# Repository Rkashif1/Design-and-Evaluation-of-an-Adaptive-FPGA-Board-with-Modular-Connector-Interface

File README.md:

**Design and Evaluation of an Adaptive FPGA Board with Modular Connector Interface**

This repository contains the complete project files for the development of an adaptive FPGA board designed to interface with various sensor and actuator peripherals through dual high-density connectors. The FPGA module is implemented using the Xilinx Spartan-7 XC7S25 and follows a modular architecture that allows it to be plugged into different motherboards for dynamic reconfiguration.

📁 Contents include:

KiCad schematic and PCB layout files

LaTeX report and documentation

Schematics and 3D board Refrence Images

🛠️ Key tools used: KiCad, Xilinx Vivado, Git, LaTeX

📌 Developed as part of an academic project demonstrating real-world modular hardware design and reconfigurable embedded systems.

*3D rendered view of the adaptive FPGA board featuring dual high-density connectors and a Spartan-7 FPGA*

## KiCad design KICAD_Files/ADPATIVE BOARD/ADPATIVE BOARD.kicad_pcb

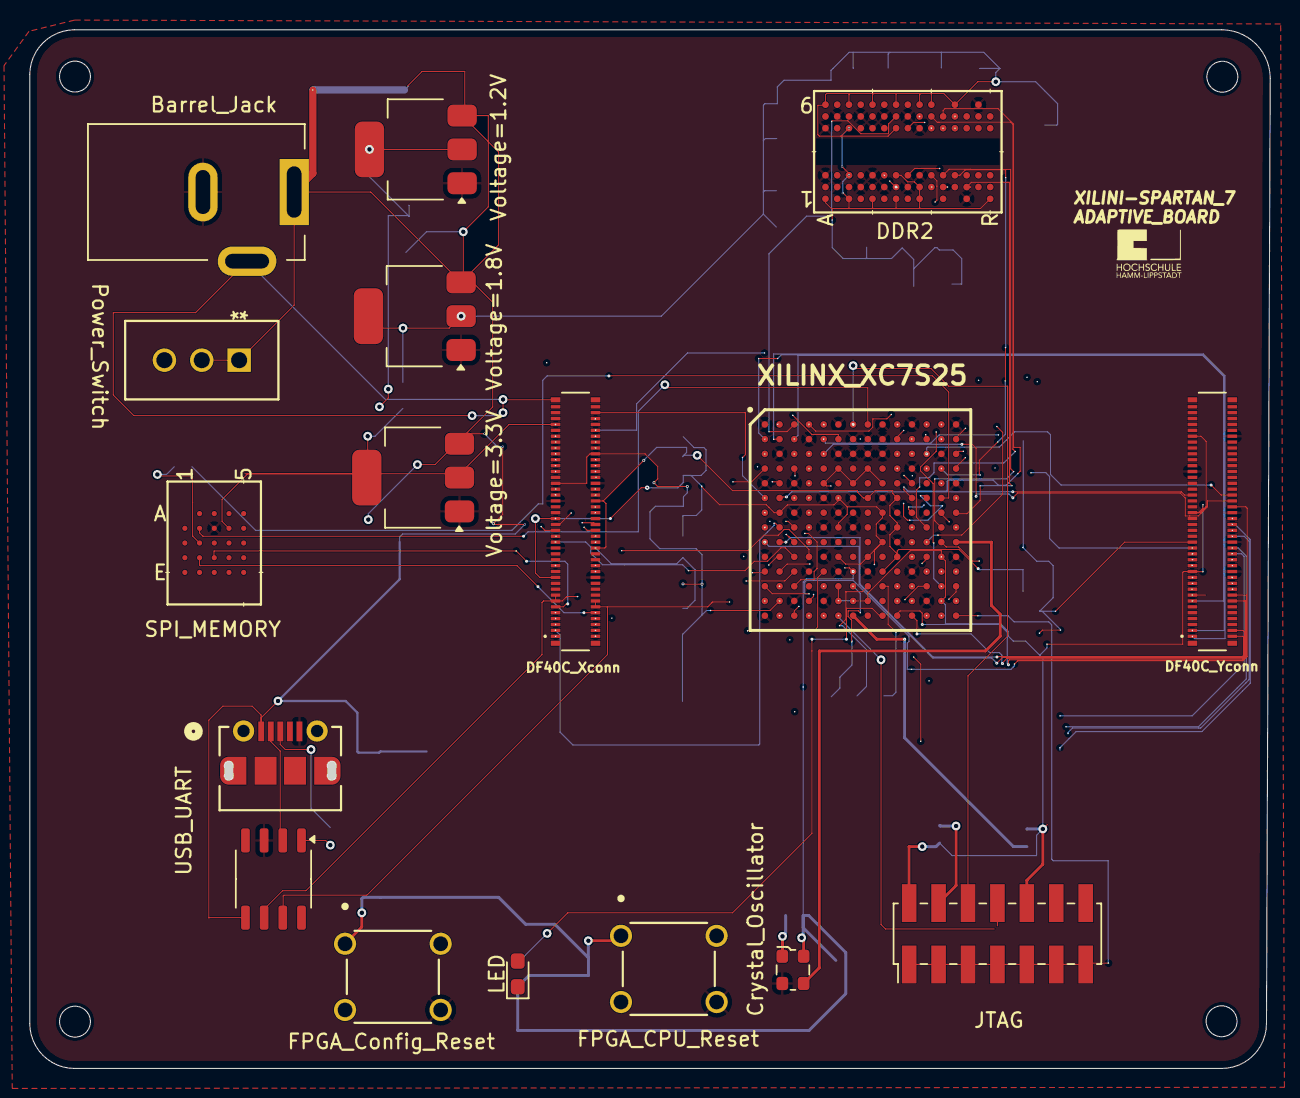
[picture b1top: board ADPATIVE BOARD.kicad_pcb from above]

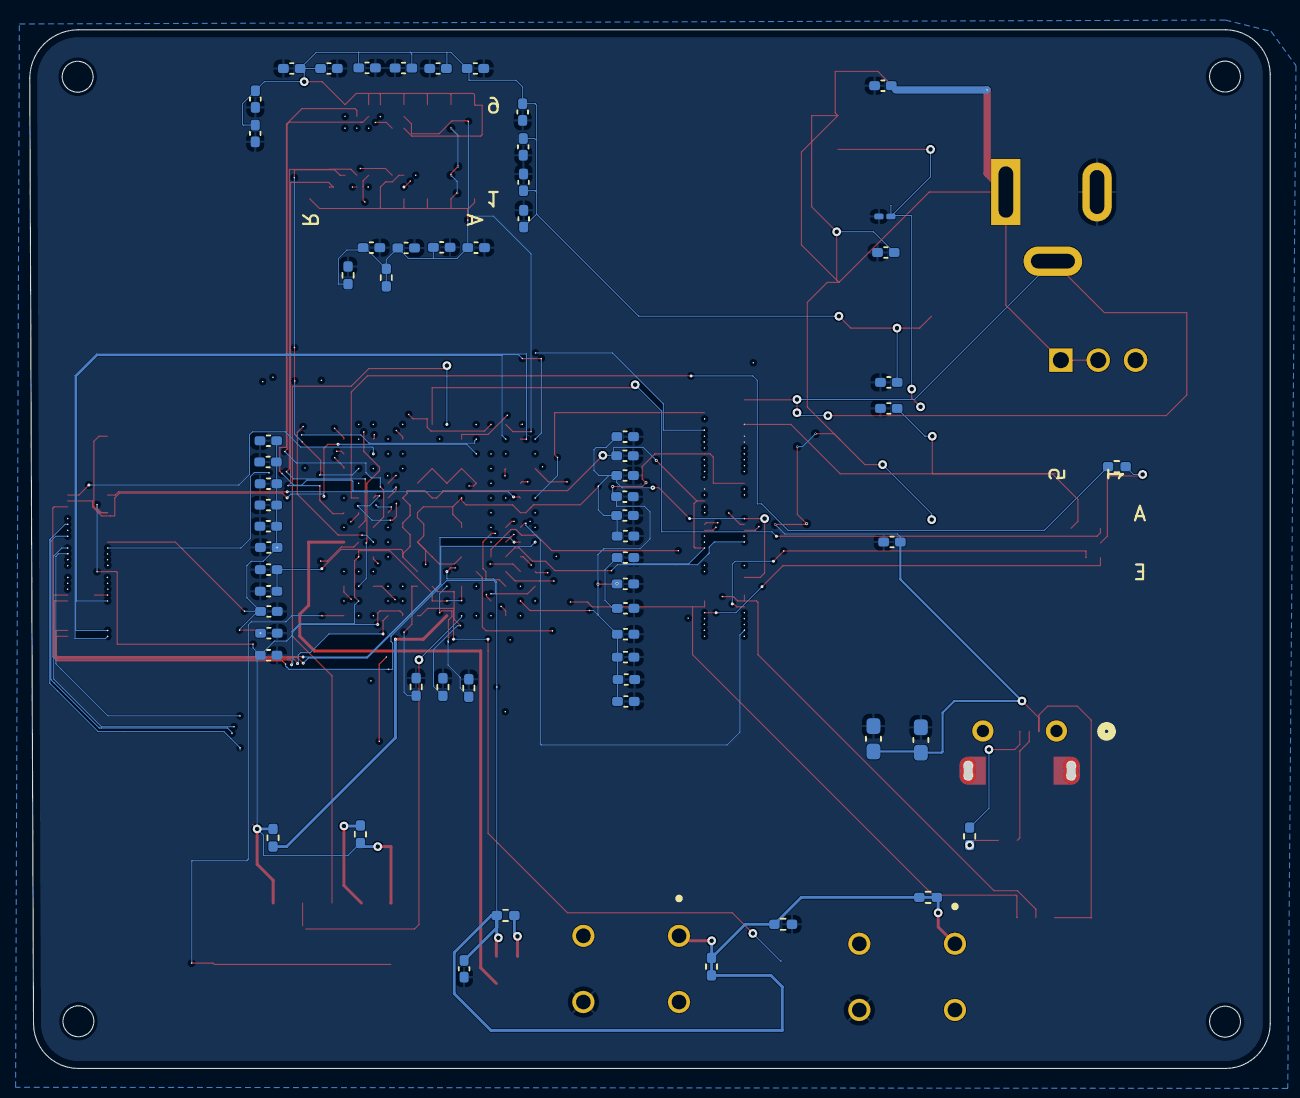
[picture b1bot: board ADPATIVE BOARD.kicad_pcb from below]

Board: 10 copper layers, 84.3 x 70.6 mm, 79 parts (62 on the bottom side), 118 nets.

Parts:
Barrel_Jack: BarrelJack_Kycon_KLDX-0202-xC_Horizontal
C1, C2, C3, C4, C5, C6, C7, C8, C9, C10, C11, C12, C13, C14, C15, C16, C17, C18, C19, C20, C21, C22, C23, C24: C_0402_1005Metric_Pad0.74x0.62mm_HandSolder
C25, C26: C; C_0603_1608Metric_Pad1.08x0.95mm_HandSolder
C27, C28, C29, C30, C31, C32, C33, C34, C35, C36, C37, C38, C39, C40, C41, C42: 100nF; C_0402_1005Metric_Pad0.74x0.62mm_HandSolder
C43: 0.1 µF; C_0402_1005Metric_Pad0.74x0.62mm_HandSolder
C44, C45, C46, C47, C48: 10µF; C_0402_1005Metric_Pad0.74x0.62mm_HandSolder
C49: 10µF; C_0201_0603Metric_Pad0.64x0.40mm_HandSolder
Crystal_Oscillator: ECS-2520MV-xxx-xx; Oscillator_SMD_ECS_2520MV-xxx-xx-4Pin_2.5x2.0mm
DDR2: MT47H32M16HR-25E:G; FBGA84_8X12P5_MRN
DF40C_Xconn, DF40C_Yconn: DF40C-80DP-0.4V_51_; HRS_DF40C-80DP-0.4V_51_
FPGA_CPU_Reset: B3F-1000; SW_B3F-1000_OMR
FPGA_Config_Reset: B3F-1000; SW_B3F-1000_OMR
JTAG: XILINX_JTAG; PinHeader_2x07_P2.00mm_Vertical_SMD
LED: LED; LED_0603_1608Metric_Pad1.05x0.95mm_HandSolder
Power_Switch: TS01CQE; TS01CQE_CNK
R1, R2, R3, R5, R10, R11, R13: 10K; R_0402_1005Metric_Pad0.72x0.64mm_HandSolder
R4: 1.5K; R_0402_1005Metric_Pad0.72x0.64mm_HandSolder
R6, R7: 1K; R_0402_1005Metric_Pad0.72x0.64mm_HandSolder
R8, R9: R; R_0402_1005Metric_Pad0.72x0.64mm_HandSolder
R12: 330; R_0402_1005Metric_Pad0.72x0.64mm_HandSolder
SPI_MEMORY: N25Q128A13E1240E; MIC-LPBGA-24-12_MRN
U4: CH340N; SOP-8_3.9x4.9mm_P1.27mm
USB_UART: 1050170001; CONN_1050170001_MOL
Voltage=1.2V: AMS1117-1.2; SOT-223-3_TabPin2
Voltage=1.8V: AMS1117-1.8; SOT-223-3_TabPin2
Voltage=3.3V: AMS1117-3.3; SOT-223-3_TabPin2
XILINX_XC7S25: XC7S25-1FTGB196C; BGA196C100P14X14_1500X1500X155

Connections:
+5V_IN: Barrel_Jack.1, C25.2, C26.1, C44.1, C45.1, C47.1, Power_Switch.1, Power_Switch.2, U4.5 (VCC), USB_UART.1, Voltage=1.2V.3 (VI), Voltage=1.8V.3 (VI), Voltage=3.3V.3 (VI)
A0: DDR2.M8 (A0), XILINX_XC7S25.D12 (IO_L8P_T1_D11_14)
A1: DDR2.M3 (A1), XILINX_XC7S25.D13 (IO_L8N_T1_D12_14)
A2: DDR2.M7 (A2), XILINX_XC7S25.E13 (IO_L10N_T1_D15_14)
A3: DDR2.N2 (A3), XILINX_XC7S25.G14 (IO_L9P_T1_DQS_14)
BA_0: DDR2.L2 (BA0), XILINX_XC7S25.H14 (IO_L14N_T2_SRCC_14)
BA_1: DDR2.L3 (BA1), XILINX_XC7S25.H13 (IO_L14P_T2_SRCC_14)
CAS*: DDR2.L7 (*CAS), XILINX_XC7S25.G11 (IO_L12P_T1_MRCC_14)
CK: DDR2.J8 (CK), XILINX_XC7S25.H11 (IO_L13P_T2_MRCC_14)
CK*: DDR2.K8 (*CK), XILINX_XC7S25.H12 (IO_L13N_T2_MRCC_14)
CKE: DDR2.K2 (CKE), XILINX_XC7S25.D10 (IO_L2P_T0_D02_14)
CLK: DF40C_Xconn.9, SPI_MEMORY.B2 (C), XILINX_XC7S25.A8 (CCLK_0)
CLK_OUTPUT: Crystal_Oscillator.3 (OUT), XILINX_XC7S25.J14 (IO_L18N_T2_D27_14)
CPU_RST: C43.1, C48.1, Crystal_Oscillator.4 (VDD), DF40C_Xconn.73, FPGA_CPU_Reset.1, FPGA_Config_Reset.1, LED.1 (K), R10.1, R10.2, R11.1, R11.2, R12.1, R13.1, SPI_MEMORY.B4 (VCC), Voltage=3.3V.2 (VO), XILINX_XC7S25.L7 (PROGRAM_B_0), XILINX_XC7S25.M14 (IO_L21N_T3_DQS_D22_14)
CS*: DDR2.L8 (*CS), XILINX_XC7S25.F11 (IO_L12N_T1_MRCC_14)
DONE_0: LED.2 (A), XILINX_XC7S25.P9 (DONE_0)
DQS_0: DDR2.G8 (DQ0), XILINX_XC7S25.A3 (IO_L2N_T0_34)
DQS_1: DDR2.G2 (DQ1), XILINX_XC7S25.A4 (IO_L2P_T0_34)
DQS_2: DDR2.H7 (DQ2), XILINX_XC7S25.A12 (IO_L4P_T0_D04_14)
DQS_3: DDR2.H3 (DQ3), XILINX_XC7S25.A13 (IO_L4N_T0_D05_14)
FPGA_RX: DF40C_Xconn.12, DF40C_Xconn.14, U4.7 (RXD), XILINX_XC7S25.P12 (IO_L22P_T3_D21_14)
FPGA_TX: DF40C_Xconn.13, DF40C_Xconn.15, U4.6 (TXD), XILINX_XC7S25.P13 (IO_L22N_T3_D20_14)
GND_FPGA_0: Barrel_Jack.2, C1.2, C2.2, C3.2, C4.1, C5.2, C6.1, C7.2, C8.2, C9.2, C10.2, C11.2, C12.2, C13.1, C14.1, C15.2, C16.1, C17.1, C18.2, C19.1, C20.1, C21.1, C22.1, C23.1, C24.2, C25.1, C26.2, C27.2, C28.2, C29.2, C30.1, C31.1, C32.2, C33.2, C34.2, C35.1, C36.2, C37.1, C38.2, C39.2, C40.2, C41.2, C42.2, C43.2, C44.2, C45.2, C46.2, C47.2, C48.2, C49.2, Crystal_Oscillator.2 (GND), DDR2.A3 (VSS), DDR2.A7 (VSSQ), DDR2.B2 (VSSQ), DDR2.B8 (VSSQ), DDR2.D2 (VSSQ), DDR2.D8 (VSSQ), DDR2.E3 (VSS), DDR2.E7 (VSSQ), DDR2.F2 (VSSQ), DDR2.F8 (VSSQ), DDR2.H2 (VSSQ), DDR2.H8 (VSSQ), DDR2.J3 (VSS), DDR2.J7 (VSSDL), DDR2.N1 (VSS), DDR2.P9 (VSS), DF40C_Xconn.22, DF40C_Xconn.31, DF40C_Xconn.42, DF40C_Xconn.47, DF40C_Xconn.54, DF40C_Yconn.24, DF40C_Yconn.34, DF40C_Yconn.44, DF40C_Yconn.57, DF40C_Yconn.70, FPGA_CPU_Reset.4, FPGA_Config_Reset.4, R1.1, R2.1, R3.1, R7.2, R12.2, SPI_MEMORY.B3 (VSS), U4.3 (GND), USB_UART.5, Voltage=1.2V.1 (GND), Voltage=1.8V.1 (GND), Voltage=3.3V.1 (GND), XILINX_XC7S25.A1 (GND_1), XILINX_XC7S25.A6 (GND_2), XILINX_XC7S25.A9 (GND_3), XILINX_XC7S25.A11 (GND_4), XILINX_XC7S25.A14 (GND_5), XILINX_XC7S25.B4 (GND_6), XILINX_XC7S25.B7 (GND_7), XILINX_XC7S25.B8 (VCCBATT_0), XILINX_XC7S25.B9 (GND_8), XILINX_XC7S25.C2 (GND_9), XILINX_XC7S25.C6 (GND_10), XILINX_XC7S25.C7 (GND_11), XILINX_XC7S25.C8 (GND_12), XILINX_XC7S25.C9 (GND_13), XILINX_XC7S25.C13 (GND_14), XILINX_XC7S25.D11 (GND_18), XILINX_XC7S25.E1 (GND_19), XILINX_XC7S25.E3 (GND_20), XILINX_XC7S25.E14 (GND_24), XILINX_XC7S25.F5 (GND_25), XILINX_XC7S25.F7 (GNDADC_0), XILINX_XC7S25.F9 (GND_26), XILINX_XC7S25.G3 (GND_27), XILINX_XC7S25.G6 (GND_28), XILINX_XC7S25.G7 (VREFN_0), XILINX_XC7S25.G10 (GND_29), XILINX_XC7S25.G12 (GND_30), XILINX_XC7S25.H5 (GND_31), XILINX_XC7S25.H7 (VN_0), XILINX_XC7S25.H9 (GND_32), XILINX_XC7S25.J6 (GND_33), XILINX_XC7S25.J10 (GND_34), XILINX_XC7S25.K1 (GND_35), XILINX_XC7S25.K5 (GND_36), XILINX_XC7S25.K14 (GND_39), XILINX_XC7S25.L4 (GND_40), XILINX_XC7S25.L6 (GND_41), XILINX_XC7S25.L8 (GND_42), XILINX_XC7S25.L11 (GND_44), XILINX_XC7S25.N3 (GND_45), XILINX_XC7S25.N5 (GND_46), XILINX_XC7S25.N12 (GND_48), XILINX_XC7S25.P1 (GND_49)
GND_JTAG: JTAG.1 (GND), JTAG.3 (GND), JTAG.5 (GND), JTAG.7 (GND), JTAG.9 (GND), JTAG.11 (GND), JTAG.13 (GND), XILINX_XC7S25.P14 (GND_50)
GPIO_1: DF40C_Xconn.1, XILINX_XC7S25.H1 (IO_L14N_T2_SRCC_34)
GPIO_2: DF40C_Xconn.2, XILINX_XC7S25.A2 (IO_L3N_T0_DQS_34)
GPIO_3: DF40C_Xconn.3, XILINX_XC7S25.H2 (IO_L14P_T2_SRCC_34)
GPIO_4: DF40C_Xconn.4, XILINX_XC7S25.P5 (IO_L24P_T3_34)
GPIO_5: DF40C_Xconn.5, XILINX_XC7S25.H3 (IO_L13N_T2_MRCC_34)
GPIO_6: DF40C_Xconn.6, XILINX_XC7S25.P4 (IO_L21P_T3_DQS_34)
GPIO_7: DF40C_Xconn.7, XILINX_XC7S25.H4 (IO_L13P_T2_MRCC_34)
GPIO_8: DF40C_Xconn.8, XILINX_XC7S25.A5 (IO_L4N_T0_34)
GPIO_24: DF40C_Xconn.24, XILINX_XC7S25.B6 (IO_0_34)
GPIO_25: DF40C_Xconn.25, XILINX_XC7S25.J11 (IO_L17P_T2_D30_14)
GPIO_26: DF40C_Xconn.26, XILINX_XC7S25.B10 (IO_L3P_T0_DQS_PUDC_B_14)
GPIO_33: DF40C_Xconn.33, XILINX_XC7S25.K3 (IO_L16N_T2_34)
GPIO_34: DF40C_Xconn.34, XILINX_XC7S25.B14 (IO_L5N_T0_D07_14)
GPIO_35: DF40C_Xconn.35, XILINX_XC7S25.K4 (IO_L16P_T2_34)
GPIO_36: DF40C_Xconn.36, XILINX_XC7S25.C1 (IO_L11N_T1_SRCC_34)
GPIO_37: DF40C_Xconn.37, XILINX_XC7S25.K11 (IO_L19P_T3_D26_14)
GPIO_38: DF40C_Xconn.38, XILINX_XC7S25.C3 (IO_L1N_T0_34)
GPIO_39: DF40C_Xconn.39, XILINX_XC7S25.K12 (IO_L19N_T3_D25_VREF_14)
GPIO_40: DF40C_Xconn.40, XILINX_XC7S25.C4 (IO_L6N_T0_VREF_34)
GPIO_44: DF40C_Xconn.44, XILINX_XC7S25.C10 (IO_L2N_T0_D03_14)
GPIO_46: DF40C_Xconn.46, XILINX_XC7S25.N14 (IO_L21P_T3_DQS_14)
GPIO_49: DF40C_Xconn.49, XILINX_XC7S25.L12 (IO_L16P_T2_CSI_B_14)
GPIO_50: DF40C_Xconn.50, XILINX_XC7S25.C14 (IO_L11N_T1_SRCC_14)
GPIO_51: DF40C_Xconn.51, XILINX_XC7S25.L13 (IO_L16N_T2_D31_14)
GPIO_52: DF40C_Xconn.52, XILINX_XC7S25.D1 (IO_L11P_T1_SRCC_34)
GPIO_56: DF40C_Xconn.56, XILINX_XC7S25.D3 (IO_L1P_T0_34)
GPIO_57: DF40C_Xconn.57, XILINX_XC7S25.M2 (IO_L19N_T3_VREF_34)
GPIO_58: DF40C_Xconn.58, XILINX_XC7S25.D4 (IO_L7N_T1_34)
GPIO_59: DF40C_Xconn.59, XILINX_XC7S25.M3 (IO_L19P_T3_34)
GPIO_60: DF40C_Xconn.60, XILINX_XC7S25.N4 (IO_L24N_T3_34)
GPIO_61: DF40C_Xconn.61, XILINX_XC7S25.M11 (IO_L20P_T3_D24_14)
GPIO_62: DF40C_Xconn.62, XILINX_XC7S25.M5 (IO_L23P_T3_34)
GPIO_63: DF40C_Xconn.63, XILINX_XC7S25.F12 (IO_L7P_T1_D09_14)
GPIO_65: DF40C_Xconn.65, XILINX_XC7S25.G4 (IO_L12P_T1_MRCC_34)
GPIO_66: DF40C_Xconn.66, XILINX_XC7S25.D14 (IO_L11P_T1_SRCC_14)
GPIO_67: DF40C_Xconn.67, XILINX_XC7S25.G1 (IO_L9P_T1_DQS_34)
GPIO_68: DF40C_Xconn.68, XILINX_XC7S25.E2 (IO_L10P_T1_34)
GPIO_69: DF40C_Xconn.69, XILINX_XC7S25.F14 (IO_L9N_T1_DQS_D13_14)
GPIO_70: DF40C_Xconn.70, XILINX_XC7S25.E4 (IO_L7P_T1_34)
GPIO_72: DF40C_Xconn.72, XILINX_XC7S25.E11 (IO_0_14)
GPIO_76: DF40C_Xconn.76, XILINX_XC7S25.M10 (IO_25_14)
GPIO_78: DF40C_Xconn.78, XILINX_XC7S25.F1 (IO_L9N_T1_DQS_34)
GPIO_Y1: DF40C_Yconn.1, XILINX_XC7S25.B2 (IO_L5P_T0_34)
GPIO_Y2: DF40C_Yconn.2, XILINX_XC7S25.J2 (IO_L15P_T2_DQS_34)
GPIO_Y3: DF40C_Yconn.3, XILINX_XC7S25.B1 (IO_L5N_T0_34)
GPIO_Y4: DF40C_Yconn.4, XILINX_XC7S25.J1 (IO_L15N_T2_DQS_34)
GPIO_Y13: DF40C_Yconn.13, XILINX_XC7S25.B3 (IO_L3P_T0_DQS_34)
GPIO_Y14: DF40C_Yconn.14, XILINX_XC7S25.P11 (IO_L24N_T3_D16_14)
GPIO_Y15: DF40C_Yconn.15, XILINX_XC7S25.P2 (IO_L20P_T3_34)
GPIO_Y16: DF40C_Yconn.16, XILINX_XC7S25.P10 (IO_L24P_T3_D17_14)
GPIO_Y17: DF40C_Yconn.17, XILINX_XC7S25.P3 (IO_L21N_T3_DQS_34)
GPIO_Y18: DF40C_Yconn.18, XILINX_XC7S25.N11 (IO_L23N_T3_D18_14)
GPIO_Y19: DF40C_Yconn.19, XILINX_XC7S25.A10 (IO_L3N_T0_DQS_EMCCLK_14)
GPIO_Y20: DF40C_Yconn.20, XILINX_XC7S25.M12 (IO_L20N_T3_D23_14)
GPIO_Y21: DF40C_Yconn.21, XILINX_XC7S25.J4 (IO_L17P_T2_34)
GPIO_Y22: DF40C_Yconn.22, XILINX_XC7S25.J3 (IO_L17N_T2_34)
GPIO_Y25: DF40C_Yconn.25, XILINX_XC7S25.B5 (IO_L4P_T0_34)
GPIO_Y26: DF40C_Yconn.26, XILINX_XC7S25.J13 (IO_L18P_T2_D28_14)
GPIO_Y27: DF40C_Yconn.27, XILINX_XC7S25.F4 (IO_L12N_T1_MRCC_34)
GPIO_Y28: DF40C_Yconn.28, XILINX_XC7S25.J12 (IO_L17N_T2_D29_14)
GPIO_Y29: DF40C_Yconn.29, XILINX_XC7S25.F3 (IO_L8P_T1_34)
GPIO_Y30: DF40C_Yconn.30, XILINX_XC7S25.N1 (IO_L20N_T3_34)
GPIO_Y31: DF40C_Yconn.31, XILINX_XC7S25.B13 (IO_L5P_T0_D06_14)
GPIO_Y32: DF40C_Yconn.32, XILINX_XC7S25.L1 (IO_L18N_T2_34)
GPIO_Y36: DF40C_Yconn.36, XILINX_XC7S25.L3 (IO_L22P_T3_34)
GPIO_Y38: DF40C_Yconn.38, XILINX_XC7S25.L2 (IO_L22N_T3_34)
GPIO_Y40: DF40C_Yconn.40, XILINX_XC7S25.L5 (IO_25_34)
GPIO_Y42: DF40C_Yconn.42, XILINX_XC7S25.N10 (IO_L23P_T3_D19_14)
GPIO_Y46: DF40C_Yconn.46, XILINX_XC7S25.M1 (IO_L18P_T2_34)
GPIO_Y48: DF40C_Yconn.48, XILINX_XC7S25.C5 (IO_L6P_T0_34)
GPIO_Y49: DF40C_Yconn.49, XILINX_XC7S25.F2 (IO_L8N_T1_34)
GPIO_Y50: DF40C_Yconn.50, XILINX_XC7S25.C12 (IO_L6N_T0_D08_VREF_14)
LDM: DDR2.F3 (LDM), XILINX_XC7S25.C11 (IO_L6P_T0_FCS_B_14)
MISO: DF40C_Xconn.10, SPI_MEMORY.D2 (DQ1), XILINX_XC7S25.B12 (IO_L1N_T0_D01_DIN_14)
MOSI: DF40C_Xconn.11, SPI_MEMORY.D3 (DQ0), XILINX_XC7S25.B11 (IO_L1P_T0_D00_MOSI_14)
unnamed: R1.2, XILINX_XC7S25.M7 (M0_0)
unnamed: R2.2, XILINX_XC7S25.M8 (M1_0)
unnamed: R3.2, XILINX_XC7S25.M9 (M2_0)
unnamed: R4.2, USB_UART.3
unnamed: JTAG.4 (TMS), R9.1
unnamed: R4.1, U4.1 (UD+)
unnamed: U4.2 (UD-), USB_UART.2
unnamed: R5.2, SPI_MEMORY.C2 (*S)
unnamed: Crystal_Oscillator.1 (Tri-State), R13.2
RAS*: DDR2.K7 (*RAS), XILINX_XC7S25.L14 (IO_L15N_T2_DQS_DOUT_CSO_B_14)
SS: R5.1, XILINX_XC7S25.F13 (IO_L10P_T1_D14_14)
TCK: JTAG.6 (TCK), XILINX_XC7S25.A7 (TCK_0)
TDI: R8.2, XILINX_XC7S25.P7 (TDI_0)
TDO: JTAG.8 (TDO), XILINX_XC7S25.P6 (TDO_0)
TMS: C8.1, C15.1, C16.2, C20.2, C21.2, C22.2, C23.2, DF40C_Xconn.53, DF40C_Xconn.64, DF40C_Yconn.23, DF40C_Yconn.43, DF40C_Yconn.69, JTAG.2 (VREF), JTAG.10 (TDI), R8.1, R9.2, XILINX_XC7S25.G13 (VCCO_14_1), XILINX_XC7S25.K2 (VCCO_34_2), XILINX_XC7S25.K13 (VCCO_14_2), XILINX_XC7S25.M6 (TMS_0), XILINX_XC7S25.N2 (VCCO_34_3), XILINX_XC7S25.N6 (VCCO_0_1), XILINX_XC7S25.N7 (CFGBVS_0), XILINX_XC7S25.N8 (VCCO_0_2), XILINX_XC7S25.N13 (VCCO_14_3)
VCCAUX: C27.1, C28.1, C29.1, C30.2, C31.2, C32.1, C33.1, C34.1, C35.2, C36.1, C37.2, C38.1, C39.1, C40.1, C41.1, C42.1, C46.1, DDR2.A1 (VDD), DDR2.A9 (VDDQ), DDR2.C1 (VDDQ), DDR2.C3 (VDDQ), DDR2.C7 (VDDQ), DDR2.C9 (VDDQ), DDR2.E1 (VDD), DDR2.E9 (VDDQ), DDR2.G1 (VDDQ), DDR2.G3 (VDDQ), DDR2.G7 (VDDQ), DDR2.G9 (VDDQ), DDR2.J1 (VDDL), DDR2.J2 (VREF), DDR2.J9 (VDD), DDR2.K9 (ODT), DDR2.M9 (VDD), DDR2.R1 (VDD), R6.1, R6.2, R7.1, Voltage=1.8V.2 (VO)
VCCAUX: C4.2, C9.1, C14.2, C18.1, C19.2, DF40C_Xconn.32, DF40C_Xconn.48, XILINX_XC7S25.F8 (VCCADC_0), XILINX_XC7S25.F10 (VCCAUX_1), XILINX_XC7S25.H10 (VCCAUX_2), XILINX_XC7S25.K10 (VCCAUX_3), XILINX_XC7S25.L9 (VCCAUX_4)
VCCINT: C1.1, C2.1, C3.1, C5.1, C6.2, C7.1, C10.1, C11.1, C12.1, C13.2, C17.2, C24.1, C49.1, DF40C_Xconn.21, DF40C_Xconn.41, DF40C_Yconn.33, Voltage=1.2V.2 (VO), XILINX_XC7S25.D6 (VCCINT_1), XILINX_XC7S25.D8 (VCCINT_2), XILINX_XC7S25.E5 (VCCBRAM_1), XILINX_XC7S25.E7 (VCCINT_3), XILINX_XC7S25.E9 (VCCINT_4), XILINX_XC7S25.F6 (VCCINT_5), XILINX_XC7S25.G2 (VCCO_34_1), XILINX_XC7S25.G9 (VCCINT_6), XILINX_XC7S25.H6 (VCCINT_7), XILINX_XC7S25.J9 (VCCINT_8), XILINX_XC7S25.K6 (VCCINT_9), XILINX_XC7S25.K8 (VCCINT_10)
WE*: DDR2.K3 (*WE), XILINX_XC7S25.M13 (IO_L15P_T2_DQS_RDWR_B_14)

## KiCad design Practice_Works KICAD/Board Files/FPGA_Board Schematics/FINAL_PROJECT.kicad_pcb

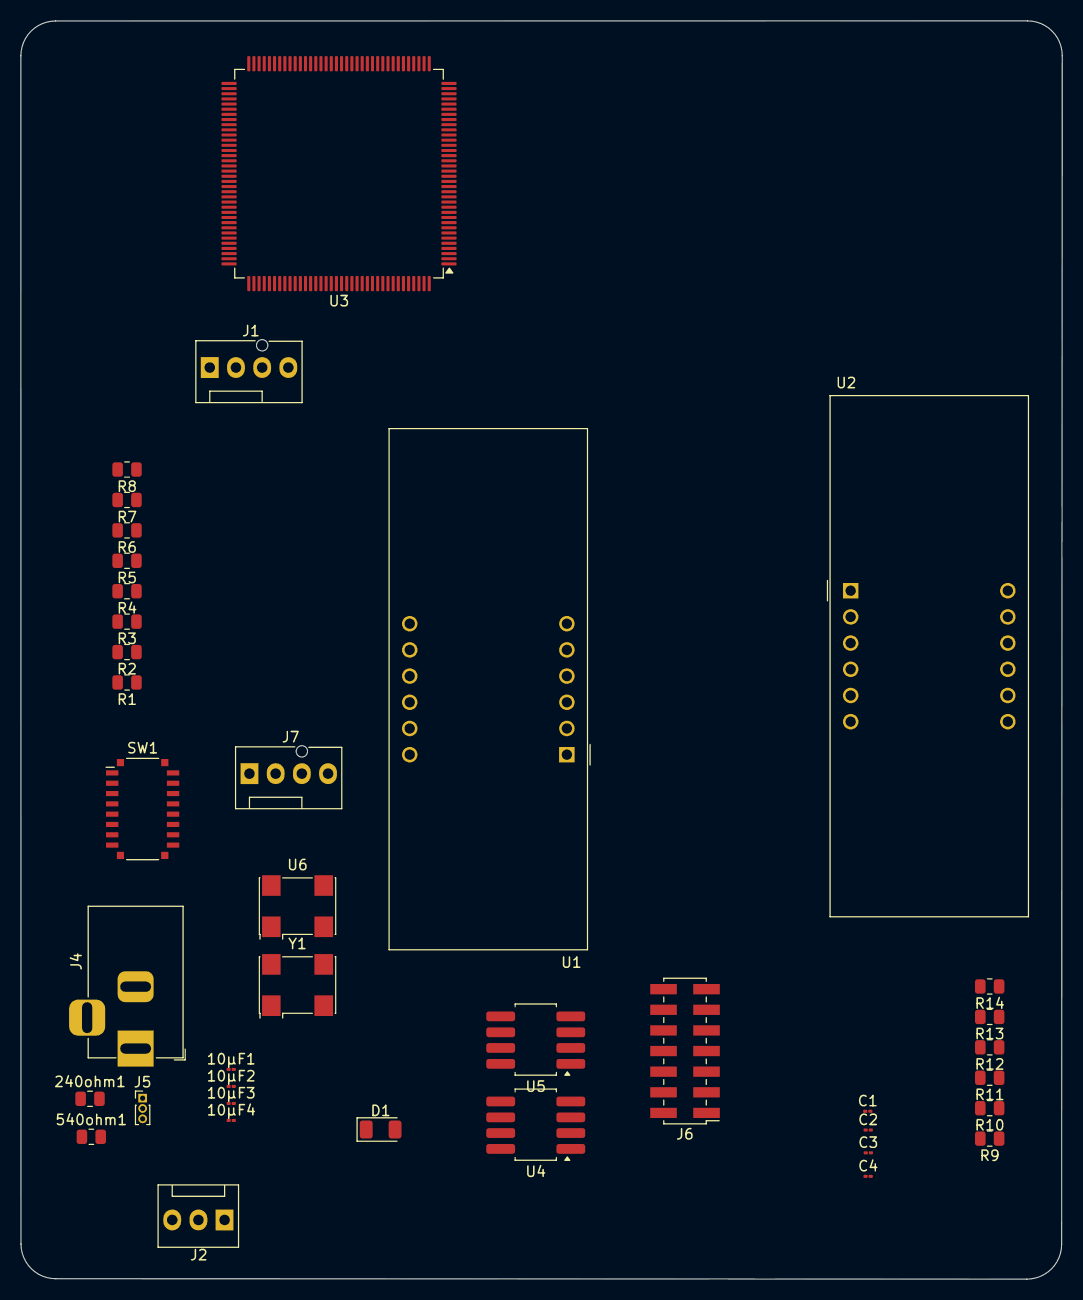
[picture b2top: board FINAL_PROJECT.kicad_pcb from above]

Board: 2 copper layers, 101.0 x 122.0 mm, 39 parts (0 on the bottom side), 39 nets, no tracks yet.

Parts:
10µF1: C1; C_01005_0402Metric
10µF2: C2; C_01005_0402Metric
10µF3, 10µF4: C3; C_01005_0402Metric
240ohm1: R1; R_0805_2012Metric
540ohm1: R2; R_0805_2012Metric
C1, C2, C3, C4: C; C_01005_0402Metric
D1: LED; LED_1206_3216Metric
J1, J7: Conn_01x06_Pin; FanPinHeader_1x04_P2.54mm_Vertical
J2: Conn_01x02_Pin; FanPinHeader_1x03_P2.54mm_Vertical
J4: Barrel_Jack_Switch; BarrelJack_Horizontal
J5: Conn_01x03; PinHeader_1x03_P1.00mm_Vertical
J6: XILINX_JTAG; PinHeader_2x07_P2.00mm_Vertical_SMD
R1, R2, R3, R4, R5, R6, R7, R8, R10, R11, R12, R13, R14: R; R_0805_2012Metric
R9: 10k; R_0805_2012Metric
SW1: SW_SPST; SW_DIP_SPSTx08_Slide_Copal_CVS-08xB_W5.9mm_P1mm
U1, U2: CA56-12CGKWA
U3: LFXP2-5E-5TN144; TQFP-144_20x20mm_P0.5mm
U4: LM317L; SOT-223-8
U5: LM7805; SOT-223-8
U6: Oscillator_SMD_Abracon_ASV-4Pin_7.0x5.1mm
Y1: Oscillator; Oscillator_SMD_Abracon_ASV-4Pin_7.0x5.1mm

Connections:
+3.3V: C1.1, C2.1, C3.1, C4.1, J6.2 (VREF), R9.1, R10.1, R11.2, R12.2, R13.2, R14.2, U6.1 (VCCADC), Y1.1, Y1.2
/powersupply/3.3v: 10µF2.1, 240ohm1.2, J2.2, J5.1, U4.2 (VO)
/powersupply/5v: 10µF4.1, D1.2 (A), J2.1, J5.2, U5.3 (VO)
GND: 10µF1.2, 10µF2.2, 10µF3.2, 10µF4.2, 540ohm1.1, C1.2, C2.2, C3.2, C4.2, J4.2, J5.3, J6.1 (GND), J6.3 (GND), J6.5 (GND), J6.7 (GND), J6.9 (GND), J6.11 (GND), J6.13 (GND), U5.2 (GND), U6.2 (GNDADC), U6.3 (VCCBATT), Y1.3
unnamed: 240ohm1.1, 540ohm1.2, D1.1 (K), U4.1 (ADJ)
unnamed: J1.1, U3.109 (PT28B/VREF2_1)
unnamed: J1.2, U3.110 (PT28A/VREF1_1)
unnamed: J1.3, U3.113 (PT21B)
unnamed: J1.4, U3.114 (PT20B/PCLKC1_0)
unnamed: J6.6 (TCK), R12.1
unnamed: J6.10 (TDI), R14.1
unnamed: J6.8 (TDO), R13.1
unnamed: J6.4 (TMS), R11.1
unnamed: J7.1, U6.4 (TMS)
unnamed: J4.1, SW1.1 (A)
unnamed: 10µF1.1, 10µF3.1, J4.3, SW1.2 (B), U4.3 (VI), U5.1 (VI)
unnamed: U1.12 (CA1), U3.144 (PT8A/ULC_GPLLT_IN_A)
unnamed: U1.9 (CA2), U3.143 (PT7A/VREF1_0)
unnamed: U1.8 (CA3), U3.142 (PT8B/ULC_GPLLC_IN_A)
unnamed: U1.6 (CA4), U3.141 (PT7B/VREF2_0)
unnamed: R8.1, U1.3 (DPX)
unnamed: R1.1, U1.11 (a)
unnamed: R2.1, U1.7 (b)
unnamed: R3.1, U1.4 (c)
unnamed: R4.1, U1.2 (d)
unnamed: R5.1, U1.1 (e)
unnamed: R6.1, U1.10 (f)
unnamed: R7.1, U1.5 (g)
unnamed: U2.12 (CA1), U3.138 (PT9A/ULC_GPLLT_FB_A)
unnamed: U2.9 (CA2), U3.137 (PT9B/ULC_GPLLC_FB_A)
unnamed: U2.8 (CA3), U3.134 (PT13A)
unnamed: U2.6 (CA4), U3.133 (PT13B)
unnamed: R8.2, U2.3 (DPX), U3.121 (PT18B)
unnamed: R1.2, U2.11 (a), U3.130 (PT14B)
unnamed: R2.2, R3.2, U2.4 (c), U2.7 (b), U3.127 (PT16A), U3.129 (PT15B)
unnamed: R4.2, U2.2 (d), U3.125 (PT16B)
unnamed: R5.2, U2.1 (e), U3.124 (PT17A)
unnamed: R6.2, U2.10 (f), U3.123 (PT18A)
unnamed: R7.2, U2.5 (g), U3.122 (PT17B)

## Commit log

2025-07-31 Updated data
2025-07-31 Updated Files
2025-08-04 Updated_Files
2025-08-04 Kicad_Files Added
2025-08-04 Image_Added
2025-08-04 Added_Image
